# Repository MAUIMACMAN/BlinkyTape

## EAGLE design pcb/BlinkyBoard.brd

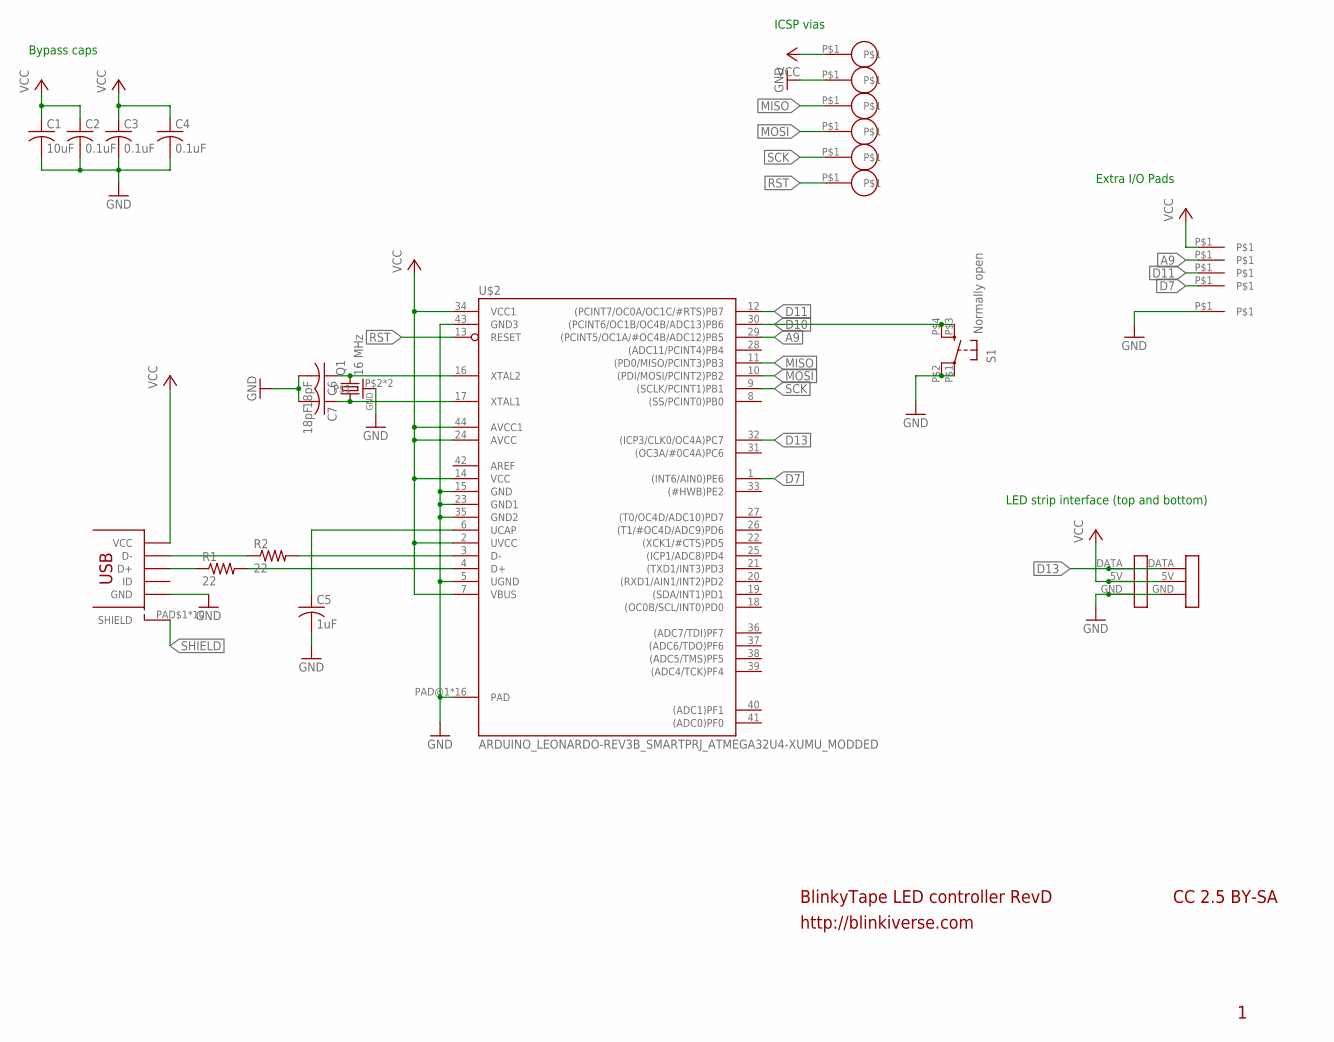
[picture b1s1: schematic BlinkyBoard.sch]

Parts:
C1: 10uF; C0603K
C2, C3, C4: 0.1uF; CAP_0402_KEMET_MEDIAN
C5: 1uF; CAP_0402_KEMET_MEDIAN
C6, C7: 18pF; CAP_0402_KEMET_MEDIAN
Q1: 16 MHz; CRSYTAL_2520
R1, R2: 22; RES_0402_KEMET_MEDIAN
S1: Normally open; GLOWBOARD_KMR211G_SWITCH
U$1, U$3, U$5, U$6, U$7, U$8: TEST_VIA; TEST_VIA_.5MM
U$2: ARDUINO_LEONARDO-REV3B_SMARTPRJ_ATMEGA32U4-XUMU_M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; QFN44ML_7X7_LONGLEADS_MOD
U$4: MICRO_USBSMT+THRUHULE; MICRO_USB_FCI_THRUHOLE
U$10, U$11, U$12, U$13, U$14: TEST_PAD_SMT
WS1, WS3: WS2811_CONNECTORSTRIP; WS2811_CONNECTOR

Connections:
A9: U$2.29 ((PCINT5/OC1A/#OC4B/ADC12)PB5), U$11.P$1
AREF: U$2.42 (AREF)
D7: U$2.1 ((INT6/AIN0)PE6), U$10.P$1
D10: S1.P$3 (S), S1.P$4 (S1), U$2.30 ((PCINT6/OC1B/OC4B/ADC13)PB6)
D11: U$2.12 ((PCINT7/OC0A/OC1C/#RTS)PB7), U$14.P$1
D13: U$2.32 ((ICP3/CLK0/OC4A)PC7), WS1.DATA, WS3.DATA
D+: R1.P$2 (2), U$2.4 (D+)
D+_IN: R1.P$1 (1), U$4.PIN$3 (D+)
D-: R2.P$2 (2), U$2.3 (D-)
D-_IN: R2.P$1 (1), U$4.PIN$2 (D-)
GND: C1.2, C2.P$2 (2), C3.P$2 (2), C4.P$2 (2), C5.P$2 (2), C6.P$2 (2), C7.P$2 (2), Q1.P$2, Q1.P$4, S1.P$1, S1.P$2 (P1), U$2.5 (UGND), U$2.15 (GND), U$2.23 (GND1), U$2.35 (GND2), U$2.43 (GND3), U$2.PAD@1 (PAD), U$2.PAD@2 (PAD), U$2.PAD@3 (PAD), U$2.PAD@4 (PAD), U$2.PAD@5 (PAD), U$2.PAD@6 (PAD), U$2.PAD@7 (PAD), U$2.PAD@8 (PAD), U$2.PAD@9 (PAD), U$2.PAD@10 (PAD), U$2.PAD@11 (PAD), U$2.PAD@12 (PAD), U$2.PAD@13 (PAD), U$2.PAD@14 (PAD), U$2.PAD@15 (PAD), U$2.PAD@16 (PAD), U$4.PIN$5 (GND), U$7.P$1, U$13.P$1, WS1.GND, WS3.GND
MISO: U$1.P$1, U$2.11 ((PD0/MISO/PCINT3)PB3)
MOSI: U$2.10 ((PDI/MOSI/PCINT2)PB2), U$3.P$1
unnamed: C5.P$1 (1), U$2.6 (UCAP)
unnamed: C6.P$1 (1), Q1.P$3 (2), U$2.16 (XTAL2)
unnamed: C7.P$1 (1), Q1.P$1 (1), U$2.17 (XTAL1)
RST: U$2.13 (RESET), U$6.P$1
SCK: U$2.9 ((SCLK/PCINT1)PB1), U$5.P$1
SHIELD: U$4.PAD$1 (SHIELD), U$4.PAD$2 (SHIELD), U$4.PAD$3 (SHIELD), U$4.PAD$4 (SHIELD), U$4.PAD$5 (SHIELD), U$4.PAD$6 (SHIELD), U$4.PAD$7 (SHIELD), U$4.PAD$8 (SHIELD), U$4.PAD$9 (SHIELD), U$4.PAD$10 (SHIELD)
VCC: C1.1, C2.P$1 (1), C3.P$1 (1), C4.P$1 (1), U$2.2 (UVCC), U$2.7 (VBUS), U$2.14 (VCC), U$2.24 (AVCC), U$2.34 (VCC1), U$2.44 (AVCC1), U$4.PIN$1 (VCC), U$8.P$1, U$12.P$1, WS1.5V, WS3.5V

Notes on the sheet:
BlinkyTape LED controller RevD
http://blinkiverse.com
CC 2.5 BY-SA
Bypass caps
ICSP vias
Extra I/O Pads
LED strip interface (top and bottom)

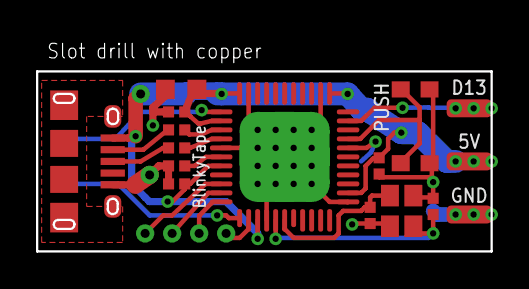
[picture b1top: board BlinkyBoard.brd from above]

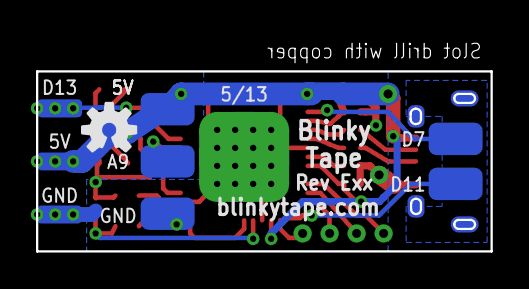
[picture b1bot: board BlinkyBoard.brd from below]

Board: 2 copper layers, 25.2 x 11.9 mm, 27 parts (7 on the bottom side), 19 nets.

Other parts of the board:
U$15: OSHW-LOGO-S

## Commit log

2013-07-26 Update Pattern Paint with a less broken save-to-strip funciton. Requires Processing 2 (because of an rxtx bug)
2013-07-27 Update Pattern Player save routine to handle RevD; add reset hook to end of program so it starts playing the animation automatically.
2013-07-27 Pattern Paint: Add small delay to exit code, to make sure the serial baud rate gets applied.
2013-09-02 Fix label: Analog input is actually on A9, not 11!
